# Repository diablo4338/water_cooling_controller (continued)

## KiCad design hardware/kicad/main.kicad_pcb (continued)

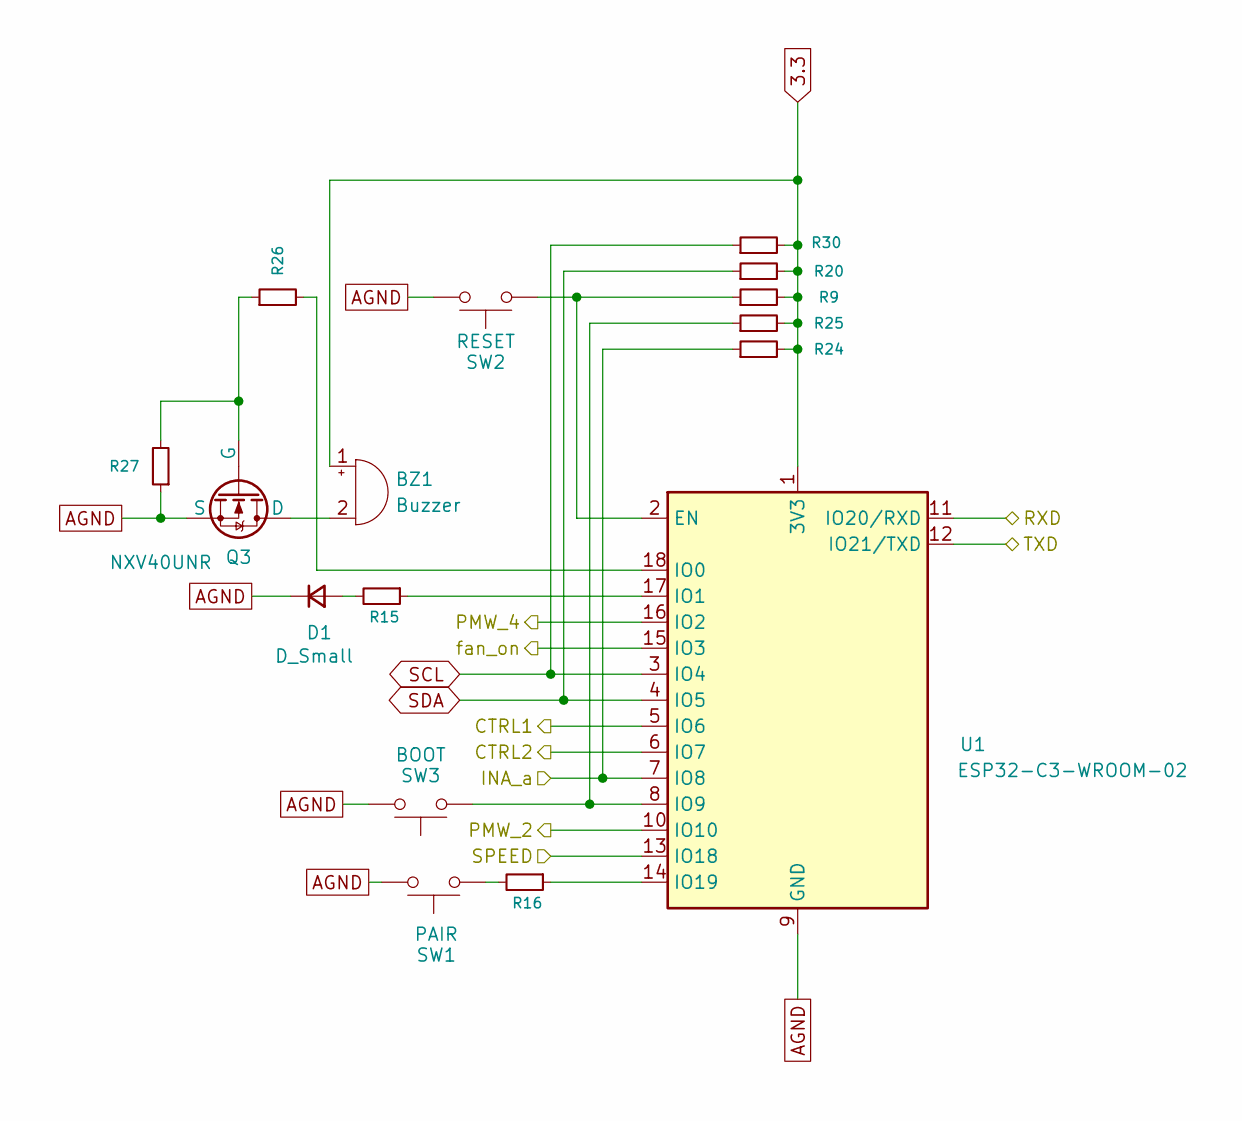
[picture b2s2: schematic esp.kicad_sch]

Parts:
BZ1: Buzzer; PinHeader_1x02_P2.54mm_Vertical
D1: D_Small; D_0805_2012Metric_Pad1.15x1.40mm_HandSolder
Q3: NXV40UNR; SOT-23-3
R9, R20, R24, R25, R30: 4k7; R_0805_2012Metric_Pad1.20x1.40mm_HandSolder
R15, R16: 1k; R_0805_2012Metric_Pad1.20x1.40mm_HandSolder
R26: 100; R_0805_2012Metric_Pad1.20x1.40mm_HandSolder
R27: 100k; R_0805_2012Metric_Pad1.20x1.40mm_HandSolder
SW1: PAIR; smd button
SW2: RESET; smd button
SW3: BOOT; smd button
U1: ESP32-C3-WROOM-02

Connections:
3.3: BZ1.1 (+), R9.2, R20.2, R24.2, R25.2, R30.2, U1.1 (3V3); also elsewhere on the board
/esp/CTRL1: U1.5 (IO6); also elsewhere on the board
/esp/CTRL2: U1.6 (IO7); also elsewhere on the board
/esp/INA_a: R24.1, U1.7 (IO8); also elsewhere on the board
/esp/PMW_2: U1.10 (IO10); also elsewhere on the board
/esp/PMW_4: U1.16 (IO2); also elsewhere on the board
/esp/RXD: U1.11 (IO20/RXD); also elsewhere on the board
/esp/SPEED: U1.13 (IO18); also elsewhere on the board
/esp/TXD: U1.12 (IO21/TXD); also elsewhere on the board
/esp/fan_on: U1.15 (IO3); also elsewhere on the board
AGND: D1.1 (K), Q3.2 (S), R27.1, SW1.2, SW2.2, SW3.2, U1.9 (GND), U1.19 (GND); also elsewhere on the board
unnamed: BZ1.2 (-), Q3.3 (D)
unnamed: D1.2 (A), R15.2
unnamed: Q3.1 (G), R26.1, R27.2
unnamed: R16.2, SW1.1
unnamed: R9.1, SW2.1, U1.2 (EN)
unnamed: R26.2, U1.18 (IO0)
unnamed: R15.1, U1.17 (IO1)
unnamed: R25.1, SW3.1, U1.8 (IO9)
unnamed: R16.1, U1.14 (IO19)
SCL: R30.1, U1.3 (IO4); also elsewhere on the board
SDA: R20.1, U1.4 (IO5); also elsewhere on the board

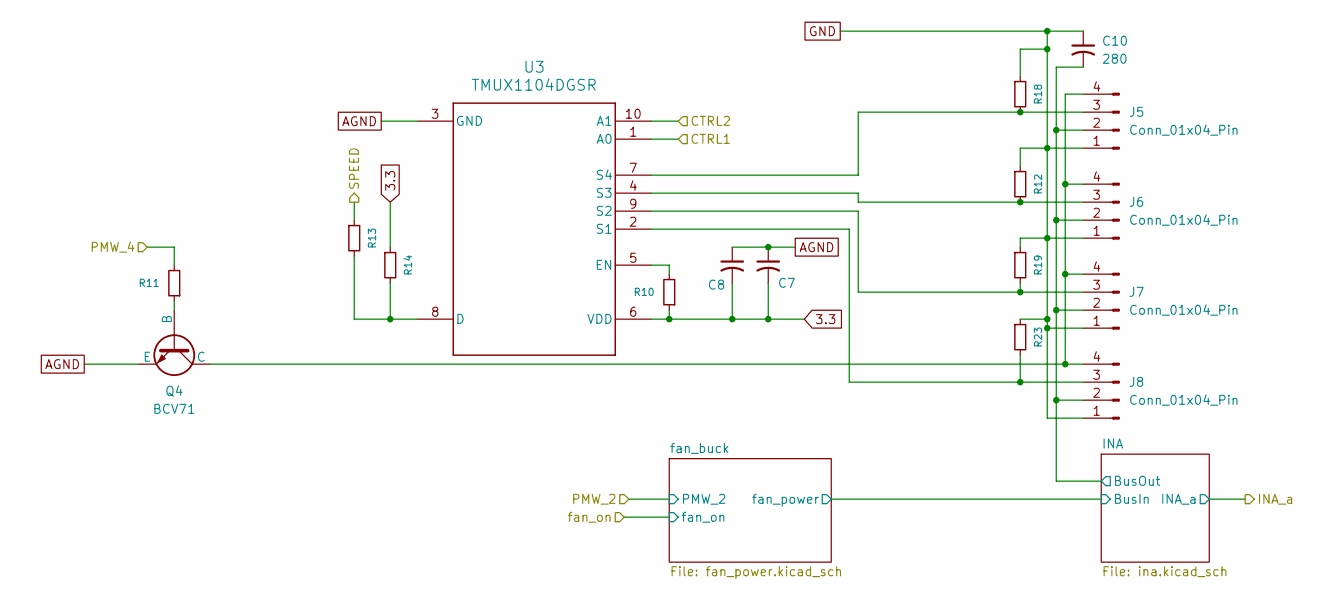
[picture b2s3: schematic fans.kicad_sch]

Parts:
C7: 1; C_0805_2012Metric_Pad1.18x1.45mm_HandSolder
C8: 0.1; C_0805_2012Metric_Pad1.18x1.45mm_HandSolder
C10: 280; CP_Radial_D8.0mm_P3.50mm
J5, J6, J7, J8: Conn_01x04_Pin; FanPinHeader_1x04_P2.54mm_Vertical
Q4: BCV71; SOT-23-3
R10, R12, R18, R19, R23: 100k; R_0805_2012Metric_Pad1.20x1.40mm_HandSolder
R11, R13: 2k2; R_0805_2012Metric_Pad1.20x1.40mm_HandSolder
R14: 4k7; R_0805_2012Metric_Pad1.20x1.40mm_HandSolder
U3: TMUX1104DGSR; DGS0010A-IPC_C

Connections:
3.3: C7.2, C8.2, R10.1, R14.1, U3.6 (VDD); also elsewhere on the board
/esp/CTRL1: U3.1 (A0); also elsewhere on the board
/esp/CTRL2: U3.10 (A1); also elsewhere on the board
/esp/PMW_4: R11.2; also elsewhere on the board
/esp/SPEED: R13.1; also elsewhere on the board
/fans/INA/BusOut: C10.2, J5.2 (VCC), J6.2 (VCC), J7.2 (VCC), J8.2 (VCC); also elsewhere on the board
AGND: C7.1, C8.1, Q4.2 (E), U3.3 (GND); also elsewhere on the board
GND: C10.1, J5.1 (GND), J6.1 (GND), J7.1 (GND), J8.1 (GND), R12.1, R18.1, R19.1, R23.1; also elsewhere on the board
unnamed: J5.4 (PMW), J6.4 (PMW), J7.4 (PMW), J8.4 (PMW), Q4.3 (C)
unnamed: J5.3 (TAHO), R18.2, U3.7 (S4)
unnamed: J6.3 (TAHO), R12.2, U3.4 (S3)
unnamed: J7.3 (TAHO), R19.2, U3.9 (S2)
unnamed: J8.3 (TAHO), R23.2, U3.2 (S1)
unnamed: Q4.1 (B), R11.1
unnamed: R13.2, R14.2, U3.8 (D)
unnamed: R10.2, U3.5 (EN)

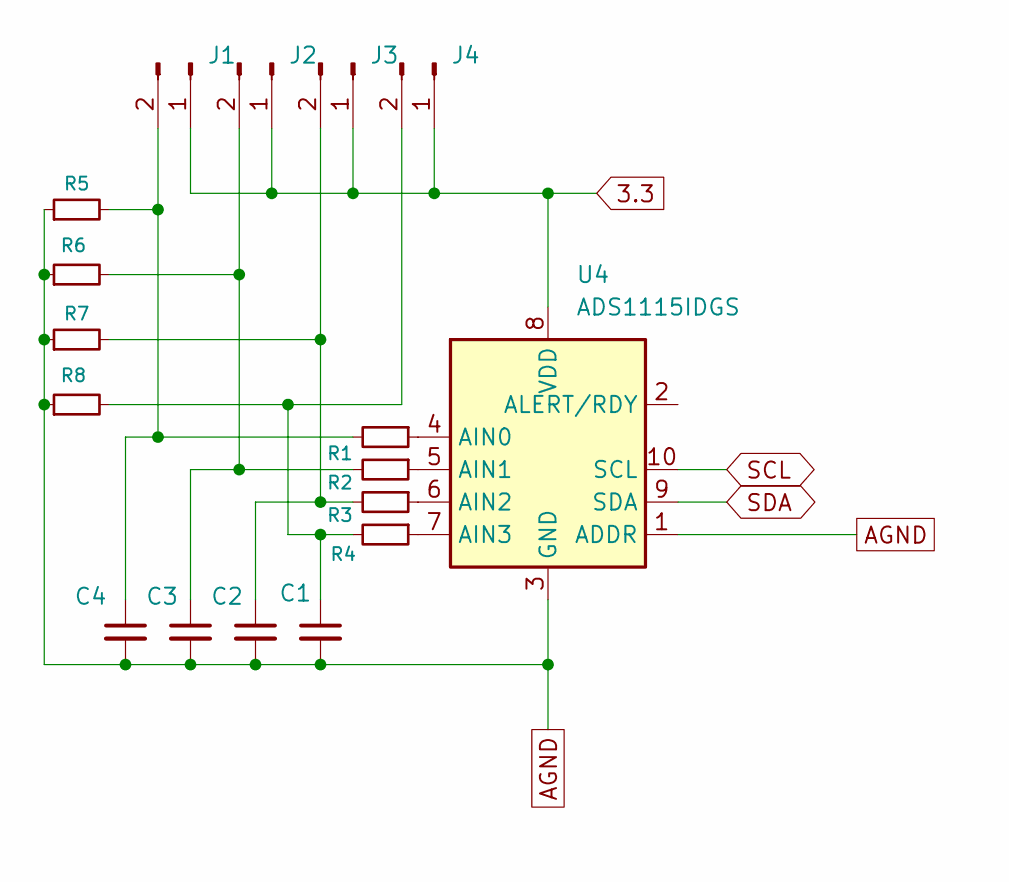
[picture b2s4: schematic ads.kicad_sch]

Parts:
C1, C2, C3, C4: 0.1; C_0805_2012Metric_Pad1.18x1.45mm_HandSolder
J1, J2, J3, J4: Conn_01x02_Pin; PinHeader_1x02_P2.54mm_Horizontal
R1, R2, R3, R4: 330; R_0805_2012Metric_Pad1.20x1.40mm_HandSolder
R5, R6, R7, R8: 4k7; R_0805_2012Metric_Pad1.20x1.40mm_HandSolder
U4: ADS1115IDGS; DGS0010A_N

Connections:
3.3: J1.1, J2.1, J3.1, J4.1, U4.8 (VDD); also elsewhere on the board
AGND: C1.2, C2.2, C3.2, C4.2, R5.1, R6.1, R7.1, R8.1, U4.1 (ADDR), U4.3 (GND); also elsewhere on the board
unnamed: C4.1, J1.2, R1.2, R5.2
unnamed: C3.1, J2.2, R2.2, R6.2
unnamed: C2.1, J3.2, R3.2, R7.2
unnamed: C1.1, J4.2, R4.2, R8.2
unnamed: R1.1, U4.4 (AIN0)
unnamed: R2.1, U4.5 (AIN1)
unnamed: R3.1, U4.6 (AIN2)
unnamed: R4.1, U4.7 (AIN3)
SCL: U4.10 (SCL); also elsewhere on the board
SDA: U4.9 (SDA); also elsewhere on the board

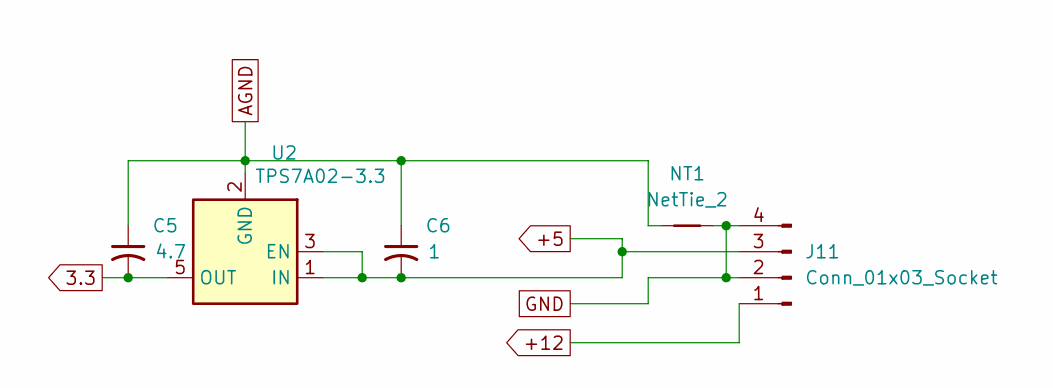
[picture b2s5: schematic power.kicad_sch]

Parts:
C5: 4.7; C_0805_2012Metric_Pad1.18x1.45mm_HandSolder
C6: 1; C_0805_2012Metric_Pad1.18x1.45mm_HandSolder
J11: Conn_01x03_Socket; sata
NT1: NetTie_2; NetTie-2_SMD_Pad0.5mm
U2: TPS7A02-3.3; SOT-23-5

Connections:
3.3: C5.2, U2.5 (OUT); also elsewhere on the board
+5: C6.2, J11.3 (+5), U2.1 (IN), U2.3 (EN); also elsewhere on the board
+12: J11.1 (+12); also elsewhere on the board
AGND: C5.1, C6.1, NT1.1, U2.2 (GND); also elsewhere on the board
GND: J11.2 (GND), J11.4 (AGND), NT1.2; also elsewhere on the board

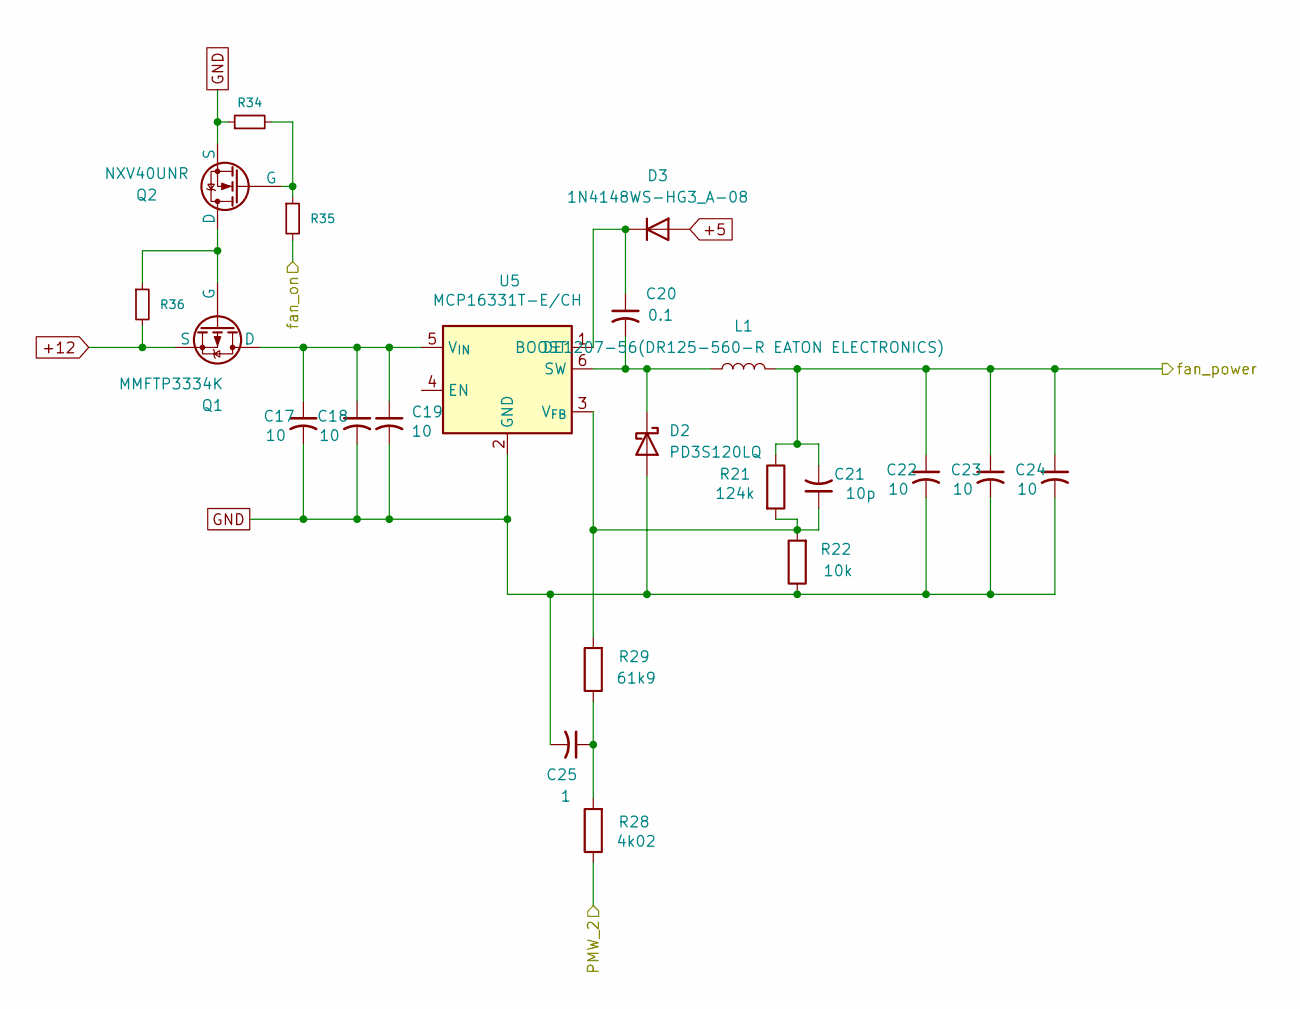
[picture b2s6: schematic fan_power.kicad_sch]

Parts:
C17, C18, C19, C22, C23, C24: 10; C_0805_2012Metric_Pad1.18x1.45mm_HandSolder
C20: 0.1; C_0805_2012Metric_Pad1.18x1.45mm_HandSolder
C21: 10p; C_0805_2012Metric_Pad1.18x1.45mm_HandSolder
C25: 1; C_0805_2012Metric_Pad1.18x1.45mm_HandSolder
D2: PD3S120LQ; 323_2
D3: 1N4148WS-HG3_A-08; D_SOD-323_HandSoldering
L1: DE1207-56(DR125-560-R EATON ELECTRONICS); SRN4018
Q1: MMFTP3334K; SOT-23-3
Q2: NXV40UNR; SOT-23-3
R21: 124k; R_0805_2012Metric_Pad1.20x1.40mm_HandSolder
R22: 10k; R_0805_2012Metric_Pad1.20x1.40mm_HandSolder
R28: 4k02; R_0805_2012Metric_Pad1.20x1.40mm_HandSolder
R29: 61k9; R_0805_2012Metric_Pad1.20x1.40mm_HandSolder
R34, R36: 100k; R_0805_2012Metric_Pad1.20x1.40mm_HandSolder
R35: 100; R_0805_2012Metric_Pad1.20x1.40mm_HandSolder
U5: MCP16331T-E/CH; SOT-23-6

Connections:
+5: D3.2 (A); also elsewhere on the board
+12: Q1.2 (S), R36.2; also elsewhere on the board
/esp/PMW_2: R28.1; also elsewhere on the board
/esp/fan_on: R35.2; also elsewhere on the board
/fans/INA/BusIn: C21.2, C22.1, C23.1, C24.1, L1.2, R21.1; also elsewhere on the board
GND: C17.2, C18.2, C19.2, C22.2, C23.2, C24.2, C25.2, D2.2 (A), Q2.2 (S), R22.1, R34.1, U5.2 (GND); also elsewhere on the board
unnamed: C25.1, R28.2, R29.1
unnamed: C20.2, D2.1 (K), L1.1, U5.6 (SW)
unnamed: C20.1, D3.1 (K), U5.1 (BOOST)
unnamed: C17.1, C18.1, C19.1, Q1.3 (D), U5.5 (V_{IN})
unnamed: Q1.1 (G), Q2.3 (D), R36.1
unnamed: Q2.1 (G), R34.2, R35.1
unnamed: C21.1, R21.2, R22.2, R29.2, U5.3 (V_{FB})

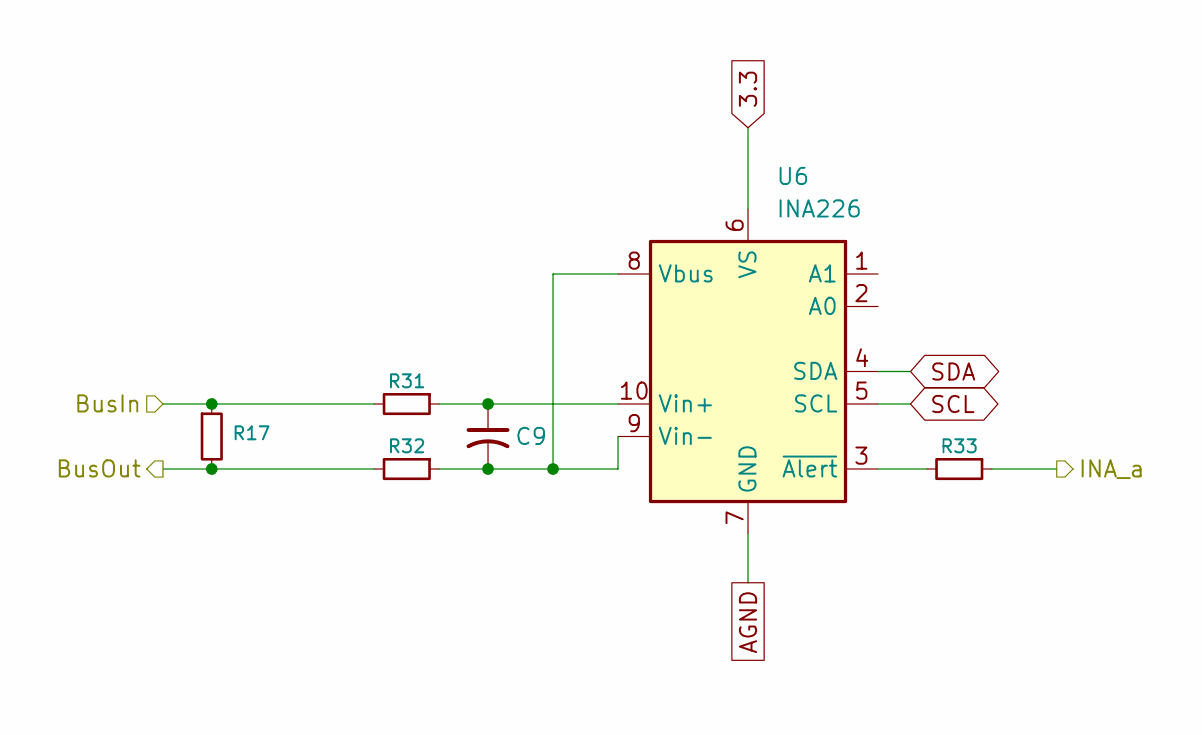
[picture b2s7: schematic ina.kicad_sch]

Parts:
C9: 0.1; C_0805_2012Metric_Pad1.18x1.45mm_HandSolder
R17: WSL2512R0470FEA; R_2512_6332Metric_Pad1.40x3.35mm_HandSolder
R31, R32: 10; R_0805_2012Metric_Pad1.20x1.40mm_HandSolder
R33: 1k; R_0805_2012Metric_Pad1.20x1.40mm_HandSolder
U6: INA226; VSSOP-10_3x3mm_P0.5mm

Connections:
3.3: U6.6 (VS); also elsewhere on the board
/esp/INA_a: R33.1; also elsewhere on the board
/fans/INA/BusIn: R17.1, R31.2; also elsewhere on the board
/fans/INA/BusOut: R17.2, R32.2; also elsewhere on the board
AGND: U6.7 (GND); also elsewhere on the board
unnamed: C9.2, R32.1, U6.8 (Vbus), U6.9 (Vin-)
unnamed: C9.1, R31.1, U6.10 (Vin+)
unnamed: R33.2, U6.3 (~Alert)
SCL: U6.5 (SCL); also elsewhere on the board
SDA: U6.4 (SDA); also elsewhere on the board

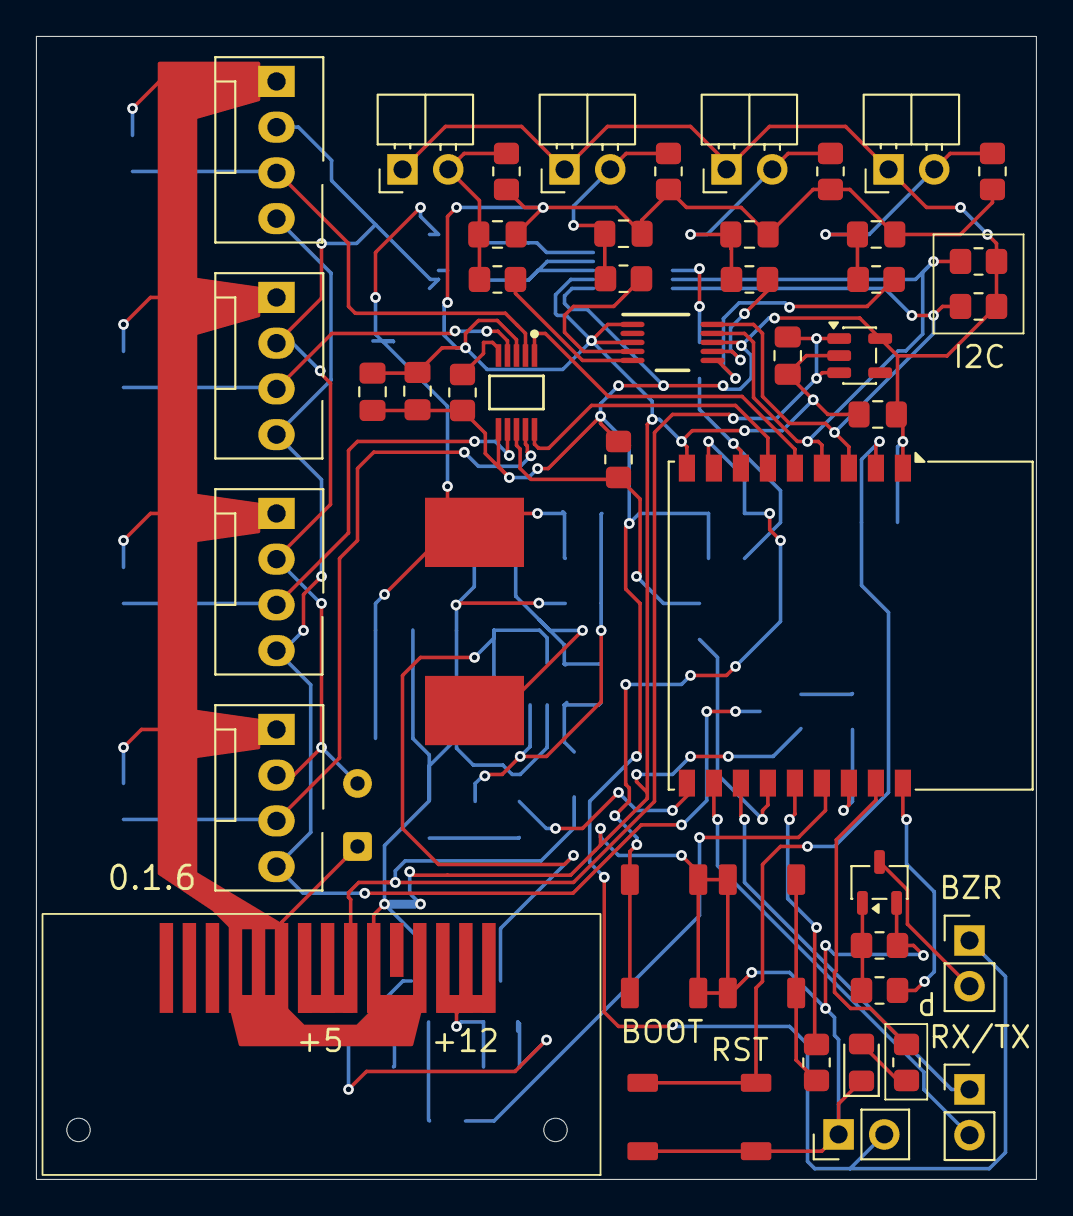
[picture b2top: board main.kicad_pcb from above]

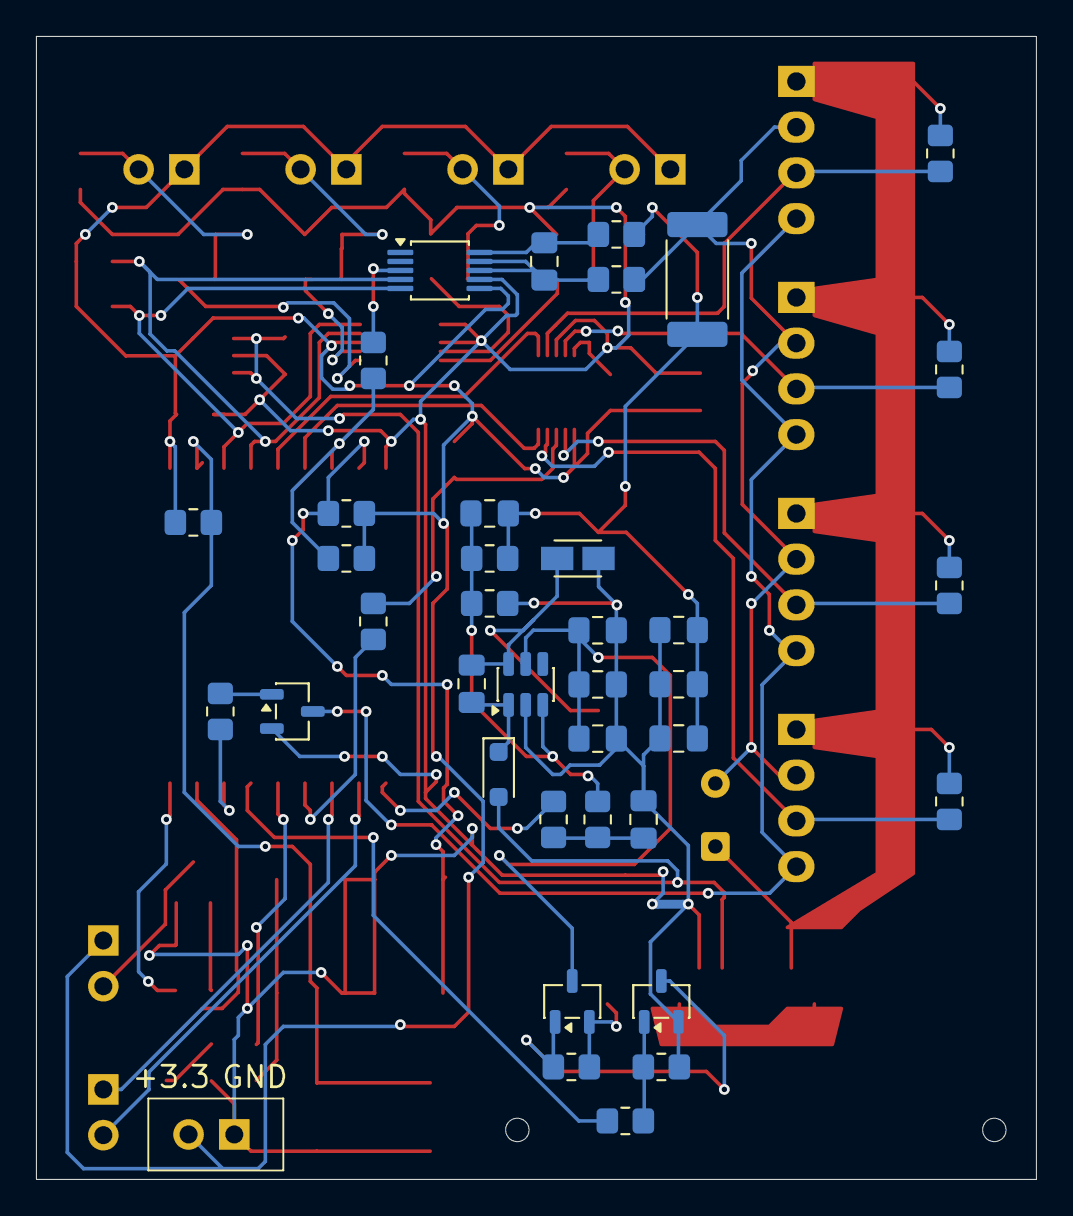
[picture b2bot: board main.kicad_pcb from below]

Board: 2 copper layers, 55.6 x 63.5 mm, 85 parts (38 on the bottom side), 53 nets.

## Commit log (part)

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2026-02-23 init
2026-02-23 Add re-pair only after reset
2026-02-23 less time to reset
2026-02-24 Move code to different files
2026-02-24 Improve pair code
2026-02-24 Improvements
2026-02-24 Improve UI
2026-02-24 Improvements, add led for debug
2026-02-24 Add retry for connect button
2026-02-24 Change debug colors
2026-02-25 Fix auth and disconnect problems
2026-02-25 Add code for simple server to test push button
2026-02-25 Add tests, refactoring
2026-02-26 Refactoring
2026-02-27 Fixes
2026-02-27 Fix log messages
2026-02-28 Fix UI
2026-02-28 Refactoring to FSM
2026-02-28 Add ads1115 adapter, remove mock service
2026-02-28 Move config to single file, handle i2c errors
2026-03-01 Add sensor threshold and init read metrics values
2026-03-01 actualize documentation
2026-03-01 change some logic inside tests
2026-03-02 fix pairing list
2026-03-02 Remove Paring action
2026-03-02 Add fan speed functional
2026-03-02 Fix tests
2026-03-12 Add params service
2026-03-12 Edit debug service
2026-03-12 Add fan control service and exceptions
2026-03-12 Add watchdog for connection
2026-03-12 Edit gitignore
2026-03-12 Add calibration operation
2026-03-12 Refactor calibration operation
2026-03-12 Refactor operation layer
2026-03-12 Refactor UI
2026-03-12 Refactor firmware code
2026-03-16 Add new parameters
2026-03-16 Make mock logic for auto-fan control
2026-03-16 Refactor operation manager
2026-03-16 Add calibration phase handling
2026-03-16 Remove unused operation
2026-03-19 Translation and complete README
2026-03-22 Fix PWM and DC
2026-04-04 Add piro firmare to test PWM
2026-04-07 Refactor pico code to raspberry
2026-04-08 Change logging strategy
2026-04-12 Change parameters, change some UI fields, finalizing fun working logic
2026-04-12 Fix fan algorithm to control
2026-04-12 UI refactoring
2026-04-12 Fix gitignore
2026-04-22 Add global FSM
2026-04-22 Add OFF mode for fan
2026-04-23 Edit calculate rpm logic
2026-04-23 Add 4 independence fans
2026-04-23 Add led indicator
2026-04-23 Refactoring device status
2026-04-24 Refactoring UI code
2026-04-24 Fix paring mode, add factory reset action
2026-04-24 Add more logs
2026-04-24 Edit timings
2026-04-25 Change UI
2026-04-25 Add overheat status
2026-04-25 Move i2c initialize procedure to independent layer
2026-04-29 Add INA226 and some UI improvements
2026-04-29 Improve INA code
2026-04-30 Improve INA code, fix overload code
2026-04-30 Add graph
2026-05-03 Add extra graph
2026-05-03 Edit UI
2026-05-03 Add default config
2026-05-03 Fix UI graph
2026-05-29 Rename saved devices
2026-05-31 UI fixes
2026-05-31 Fix metrics aggregation
2026-06-01 change rpm calculation algorithm
2026-06-01 Fix ui logs
2026-06-01 Fix shared i2c bus
2026-06-01 Fix speed calculate code
2026-06-13 Fix tests and code structure
2026-06-13 Fix structure
2026-06-13 Fix cache for release build process
2026-06-13 Reorganize file structure in project
2026-06-13 Add hardware files
2026-06-13 Edit actions files
2026-06-13 Edit production files
2026-06-13 small fixes
2026-06-14 Complete README
2026-06-15 Change deploy process, add LICENSE files
2026-06-15 Actualize production files
2026-06-15 edit actions
2026-06-19 Pack firmware to zip
2026-06-22 Change UI layout
